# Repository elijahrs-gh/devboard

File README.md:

# Devboard
A custom RP2040 devboard.

## Schematic:

## PCB:

## BOM:
| Reference                     | Qty | Value                      | DNP | Exclude from BOM | Exclude from Board | Footprint                                        | Datasheet                                                                                     |
|-------------------------------|-----|----------------------------|-----|------------------|-------------------|-------------------------------------------------|------------------------------------------------------------------------------------------------|
| C1,C10                        | 2   | 1uF                        |     |                  |                   | Capacitor_SMD:C_0402_1005Metric                  | ~                                                                                              |
| C2,C3,C4,C5,C6,C7,C8,C9,C11,C12,C17 | 11  | 0.1uF                      |     |                  |                   | Capacitor_SMD:C_0402_1005Metric                  | ~                                                                                              |
| C13,C14                      | 2   | 10uF                       |     |                  |                   | Capacitor_SMD:C_0603_1608Metric                  | ~                                                                                              |
| C15,C16                      | 2   | 33pF                       |     |                  |                   | Capacitor_SMD:C_0402_1005Metric                  | ~                                                                                              |
| J1                            | 1   | USB_C_Receptacle_USB2.0_14P |     |                  |                   | Connector_USB:USB_C_Receptacle_HRO_TYPE-C-31-M-12 | https://www.usb.org/sites/default/files/documents/usb_type-c.zip                               |
| J2,J3                        | 2   | Conn_01x20                 |     |                  |                   | Connector_PinHeader_2.54mm:PinHeader_1x20_P2.54mm_Vertical | ~                                                                                              |
| J4                            | 1   | Conn_01x03                 |     |                  |                   | Connector_PinHeader_2.54mm:PinHeader_1x03_P2.54mm_Vertical | ~                                                                                              |
| R1,R2                        | 2   | 5.1K                       |     |                  |                   | Resistor_SMD:R_0402_1005Metric                   | ~                                                                                              |
| R3,R4                        | 2   | 27                         |     |                  |                   | Resistor_SMD:R_0402_1005Metric                   | ~                                                                                              |
| R5,R7                        | 2   | 1K                         |     |                  |                   | Resistor_SMD:R_0402_1005Metric                   | ~                                                                                              |
| R6                            | 1   | 10K                        |     |                  |                   | Resistor_SMD:R_0402_1005Metric                   | ~                                                                                              |
| SW1                           | 1   | SW_Push                    |     |                  |                   | Button_Switch_SMD:SW_Push_SPST_NO_Alps_SKRK     | ~                                                                                              |
| U1                            | 1   | RP2040                     |     |                  |                   | Package_DFN_QFN:QFN-56-1EP_7x7mm_P0.4mm_EP3.2x3.2mm | https://datasheets.raspberrypi.com/rp2040/rp2040-datasheet.pdf                                |
| U2                            | 1   | NCP1117-3.3_SOT223         |     |                  |                   | Package_TO_SOT_SMD:SOT-223-3_TabPin2             | http://www.onsemi.com/pub_link/Collateral/NCP1117-D.PDF                                        |
| U3                            | 1   | W25Q16JVZPIQ TR            |     |                  |                   | Package_SON:Winbond_USON-8-1EP_3x2mm_P0.5mm_EP0.2x1.6mm | https://www.winbond.com/resource-files/w25q128jv_dtr%20revc%2003272018%20plus.pdf              |
| Y1                            | 1   | 12 MHz                     |     |                  |                   | Crystal:Crystal_SMD_3225-4Pin_3.2x2.5mm          | ~                                                                                              |

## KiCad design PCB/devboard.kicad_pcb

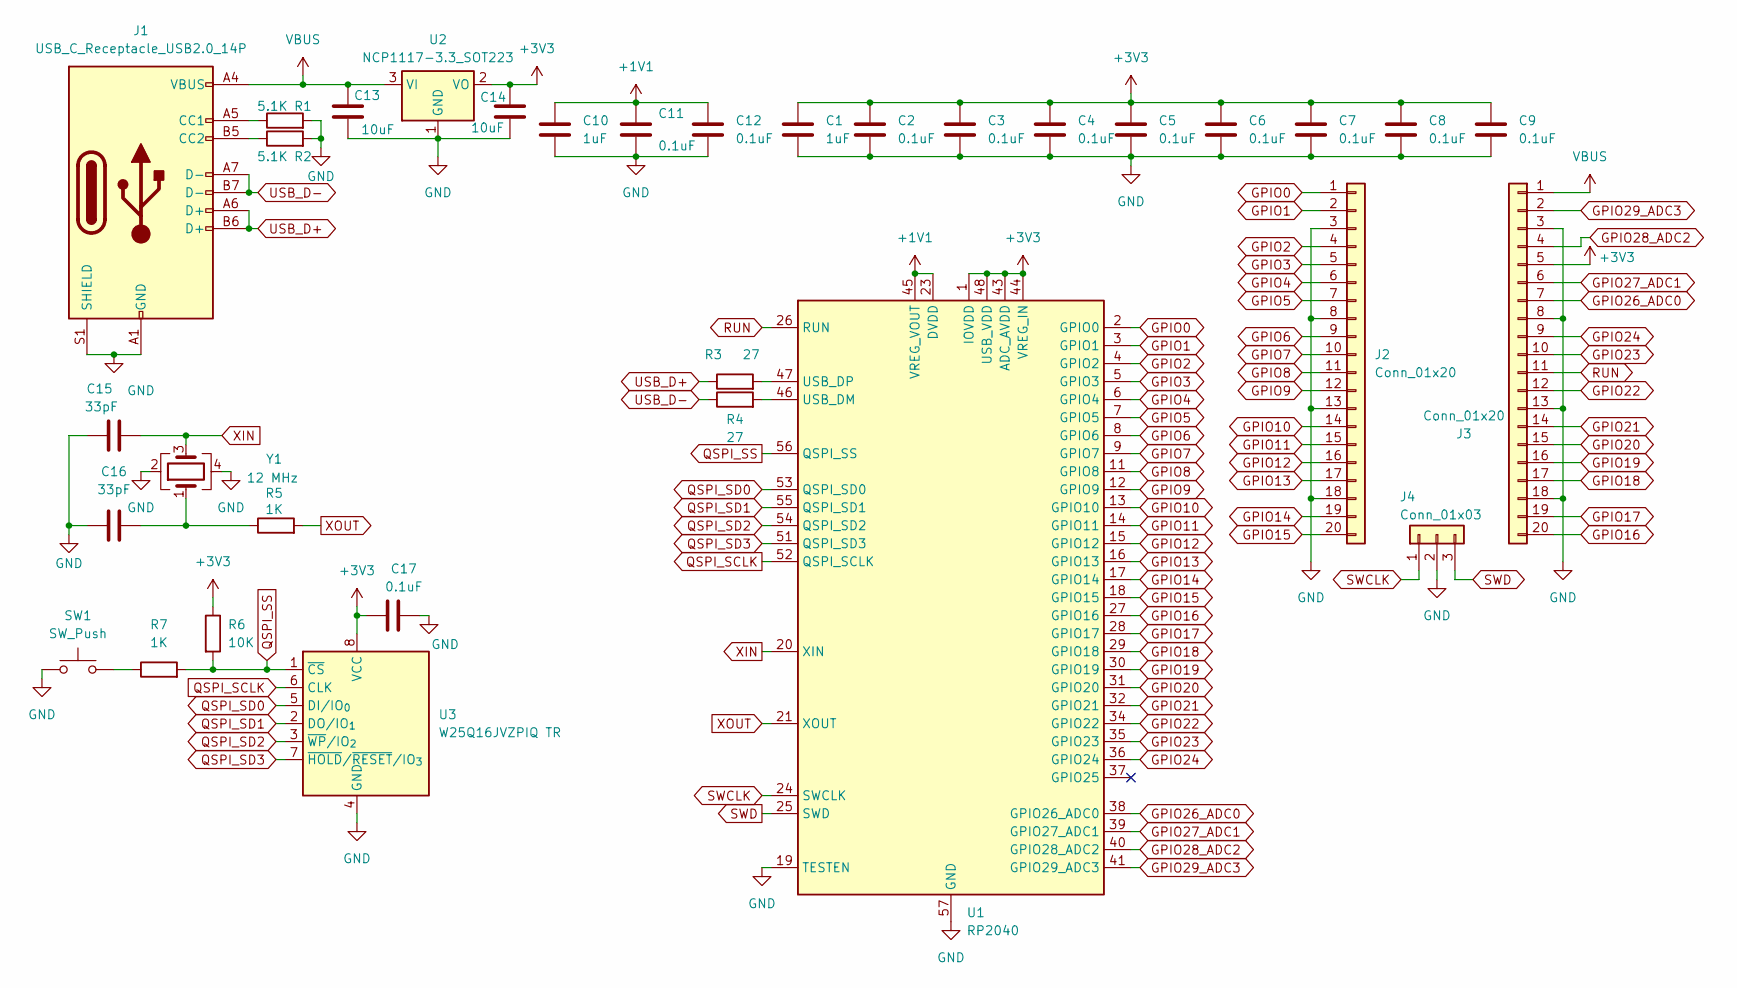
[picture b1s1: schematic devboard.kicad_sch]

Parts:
C1, C10: 1uF; C_0402_1005Metric
C2, C3, C4, C5, C6, C7, C8, C9, C11, C12, C17: 0.1uF; C_0402_1005Metric
C13, C14: 10uF; C_0603_1608Metric
C15, C16: 33pF; C_0402_1005Metric
J1: USB_C_Receptacle_USB2.0_14P; USB_C_Receptacle_HRO_TYPE-C-31-M-12
J2, J3: Conn_01x20; PinHeader_1x20_P2.54mm_Vertical
J4: Conn_01x03; PinHeader_1x03_P2.54mm_Vertical
R1, R2: 5.1K; R_0402_1005Metric
R3, R4: 27; R_0402_1005Metric
R5, R7: 1K; R_0402_1005Metric
R6: 10K; R_0402_1005Metric
SW1: SW_Push; SW_Push_SPST_NO_Alps_SKRK
U1: RP2040; QFN-56-1EP_7x7mm_P0.4mm_EP3.2x3.2mm
U2: NCP1117-3.3_SOT223; SOT-223-3_TabPin2
U3: W25Q16JVZPIQ TR; Winbond_USON-8-1EP_3x2mm_P0.5mm_EP0.2x1.6mm
Y1: 12 MHz; Crystal_SMD_3225-4Pin_3.2x2.5mm

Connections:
+1V1: C10.1, C11.1, C12.1, U1.23 (DVDD), U1.45 (VREG_VOUT), U1.50 (DVDD)
+3V3: C1.1, C2.1, C3.1, C4.1, C5.1, C6.1, C7.1, C8.1, C9.1, C14.1, C17.1, J3.5, R6.1, U1.1 (IOVDD), U1.10 (IOVDD), U1.22 (IOVDD), U1.33 (IOVDD), U1.42 (IOVDD), U1.43 (ADC_AVDD), U1.44 (VREG_IN), U1.48 (USB_VDD), U1.49 (IOVDD), U2.2 (VO), U3.8 (VCC)
GND: C1.2, C2.2, C3.2, C4.2, C5.2, C6.2, C7.2, C8.2, C9.2, C10.2, C11.2, C12.2, C13.2, C14.2, C15.1, C16.1, C17.2, J1.A1 (GND), J1.A12 (GND), J1.B1 (GND), J1.B12 (GND), J1.S1 (SHIELD), J2.3, J2.8, J2.13, J2.18, J3.3, J3.8, J3.13, J3.18, J4.2, R1.2, R2.2, SW1.1, U1.19 (TESTEN), U1.57 (GND), U2.1 (GND), U3.4 (GND), Y1.2, Y1.4
GPIO0: J2.1, U1.2 (GPIO0)
GPIO1: J2.2, U1.3 (GPIO1)
GPIO2: J2.4, U1.4 (GPIO2)
GPIO3: J2.5, U1.5 (GPIO3)
GPIO4: J2.6, U1.6 (GPIO4)
GPIO5: J2.7, U1.7 (GPIO5)
GPIO6: J2.9, U1.8 (GPIO6)
GPIO7: J2.10, U1.9 (GPIO7)
GPIO8: J2.11, U1.11 (GPIO8)
GPIO9: J2.12, U1.12 (GPIO9)
GPIO10: J2.14, U1.13 (GPIO10)
GPIO11: J2.15, U1.14 (GPIO11)
GPIO12: J2.16, U1.15 (GPIO12)
GPIO13: J2.17, U1.16 (GPIO13)
GPIO14: J2.19, U1.17 (GPIO14)
GPIO15: J2.20, U1.18 (GPIO15)
GPIO16: J3.20, U1.27 (GPIO16)
GPIO17: J3.19, U1.28 (GPIO17)
GPIO18: J3.17, U1.29 (GPIO18)
GPIO19: J3.16, U1.30 (GPIO19)
GPIO20: J3.15, U1.31 (GPIO20)
GPIO21: J3.14, U1.32 (GPIO21)
GPIO22: J3.12, U1.34 (GPIO22)
GPIO23: J3.10, U1.35 (GPIO23)
GPIO24: J3.9, U1.36 (GPIO24)
GPIO26_ADC0: J3.7, U1.38 (GPIO26_ADC0)
GPIO27_ADC1: J3.6, U1.39 (GPIO27_ADC1)
GPIO28_ADC2: J3.4, U1.40 (GPIO28_ADC2)
GPIO29_ADC3: J3.2, U1.41 (GPIO29_ADC3)
unnamed: C16.2, R5.1, Y1.1
unnamed: J1.A5 (CC1), R1.1
unnamed: J1.B5 (CC2), R2.1
unnamed: R7.1, SW1.2
unnamed: R4.2, U1.46 (USB_DM)
unnamed: R3.2, U1.47 (USB_DP)
QSPI_SCLK: U1.52 (QSPI_SCLK), U3.6 (CLK)
QSPI_SD0: U1.53 (QSPI_SD0), U3.5 (DI/IO_{0})
QSPI_SD1: U1.55 (QSPI_SD1), U3.2 (DO/IO_{1})
QSPI_SD2: U1.54 (QSPI_SD2), U3.3 (~WP/IO_{2})
QSPI_SD3: U1.51 (QSPI_SD3), U3.7 (~HOLD/~RESET/IO_{3})
QSPI_SS: R6.2, R7.2, U1.56 (QSPI_SS), U3.1 (~CS)
RUN: J3.11, U1.26 (RUN)
SWCLK: J4.1, U1.24 (SWCLK)
SWD: J4.3, U1.25 (SWD)
USB_D+: J1.A6 (D+), J1.B6 (D+), R3.1
USB_D-: J1.A7 (D-), J1.B7 (D-), R4.1
VBUS: C13.1, J1.A4 (VBUS), J1.A9 (VBUS), J1.B4 (VBUS), J1.B9 (VBUS), J3.1, U2.3 (VI)
XIN: C15.2, U1.20 (XIN), Y1.3
XOUT: R5.2, U1.21 (XOUT)

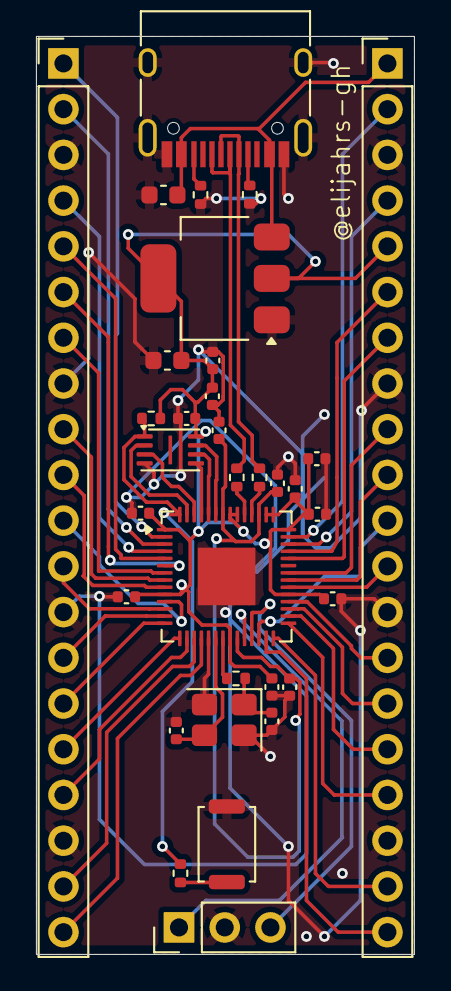
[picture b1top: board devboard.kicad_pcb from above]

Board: 2 copper layers, 21.0 x 51.0 mm, 33 parts (0 on the bottom side), 52 nets.

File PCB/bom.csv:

Designator,Footprint,Quantity,Value,LCSC Part #
"C1, C10",0402,2,1uF,
"C11, C12, C17, C2, C3, C4, C5, C6, C7, C8, C9",0402,11,0.1uF,
"C13, C14",0603,2,10uF,
"C15, C16",0402,2,33pF,
J1,USB_C_Receptacle_HRO_TYPE-C-31-M-12,1,USB_C_Receptacle_USB2.0_14P,
"J2, J3",PinHeader_1x20_P2.54mm_Vertical,2,Conn_01x20,
J4,PinHeader_1x03_P2.54mm_Vertical,1,Conn_01x03,
"R1, R2",0402,2,5.1K,
"R3, R4",0402,2,27,
"R5, R7",0402,2,1K,
R6,0402,1,10K,
SW1,SW_Push_SPST_NO_Alps_SKRK,1,SW_Push,
U1,QFN-56-1EP_7x7mm_P0.4mm_EP3.2x3.2mm,1,RP2040,
U2,SOT-223-3_TabPin2,1,NCP1117-3.3_SOT223,
U3,Winbond_USON-8-1EP_3x2mm_P0.5mm_EP0.2x1.6mm,1,W25Q16JVZPIQ TR,
Y1,Crystal_SMD_3225-4Pin_3.2x2.5mm,1,12 MHz,

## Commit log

2025-11-26 Update README with Devboard details and images
    Added images and descriptions for the Devboard.
